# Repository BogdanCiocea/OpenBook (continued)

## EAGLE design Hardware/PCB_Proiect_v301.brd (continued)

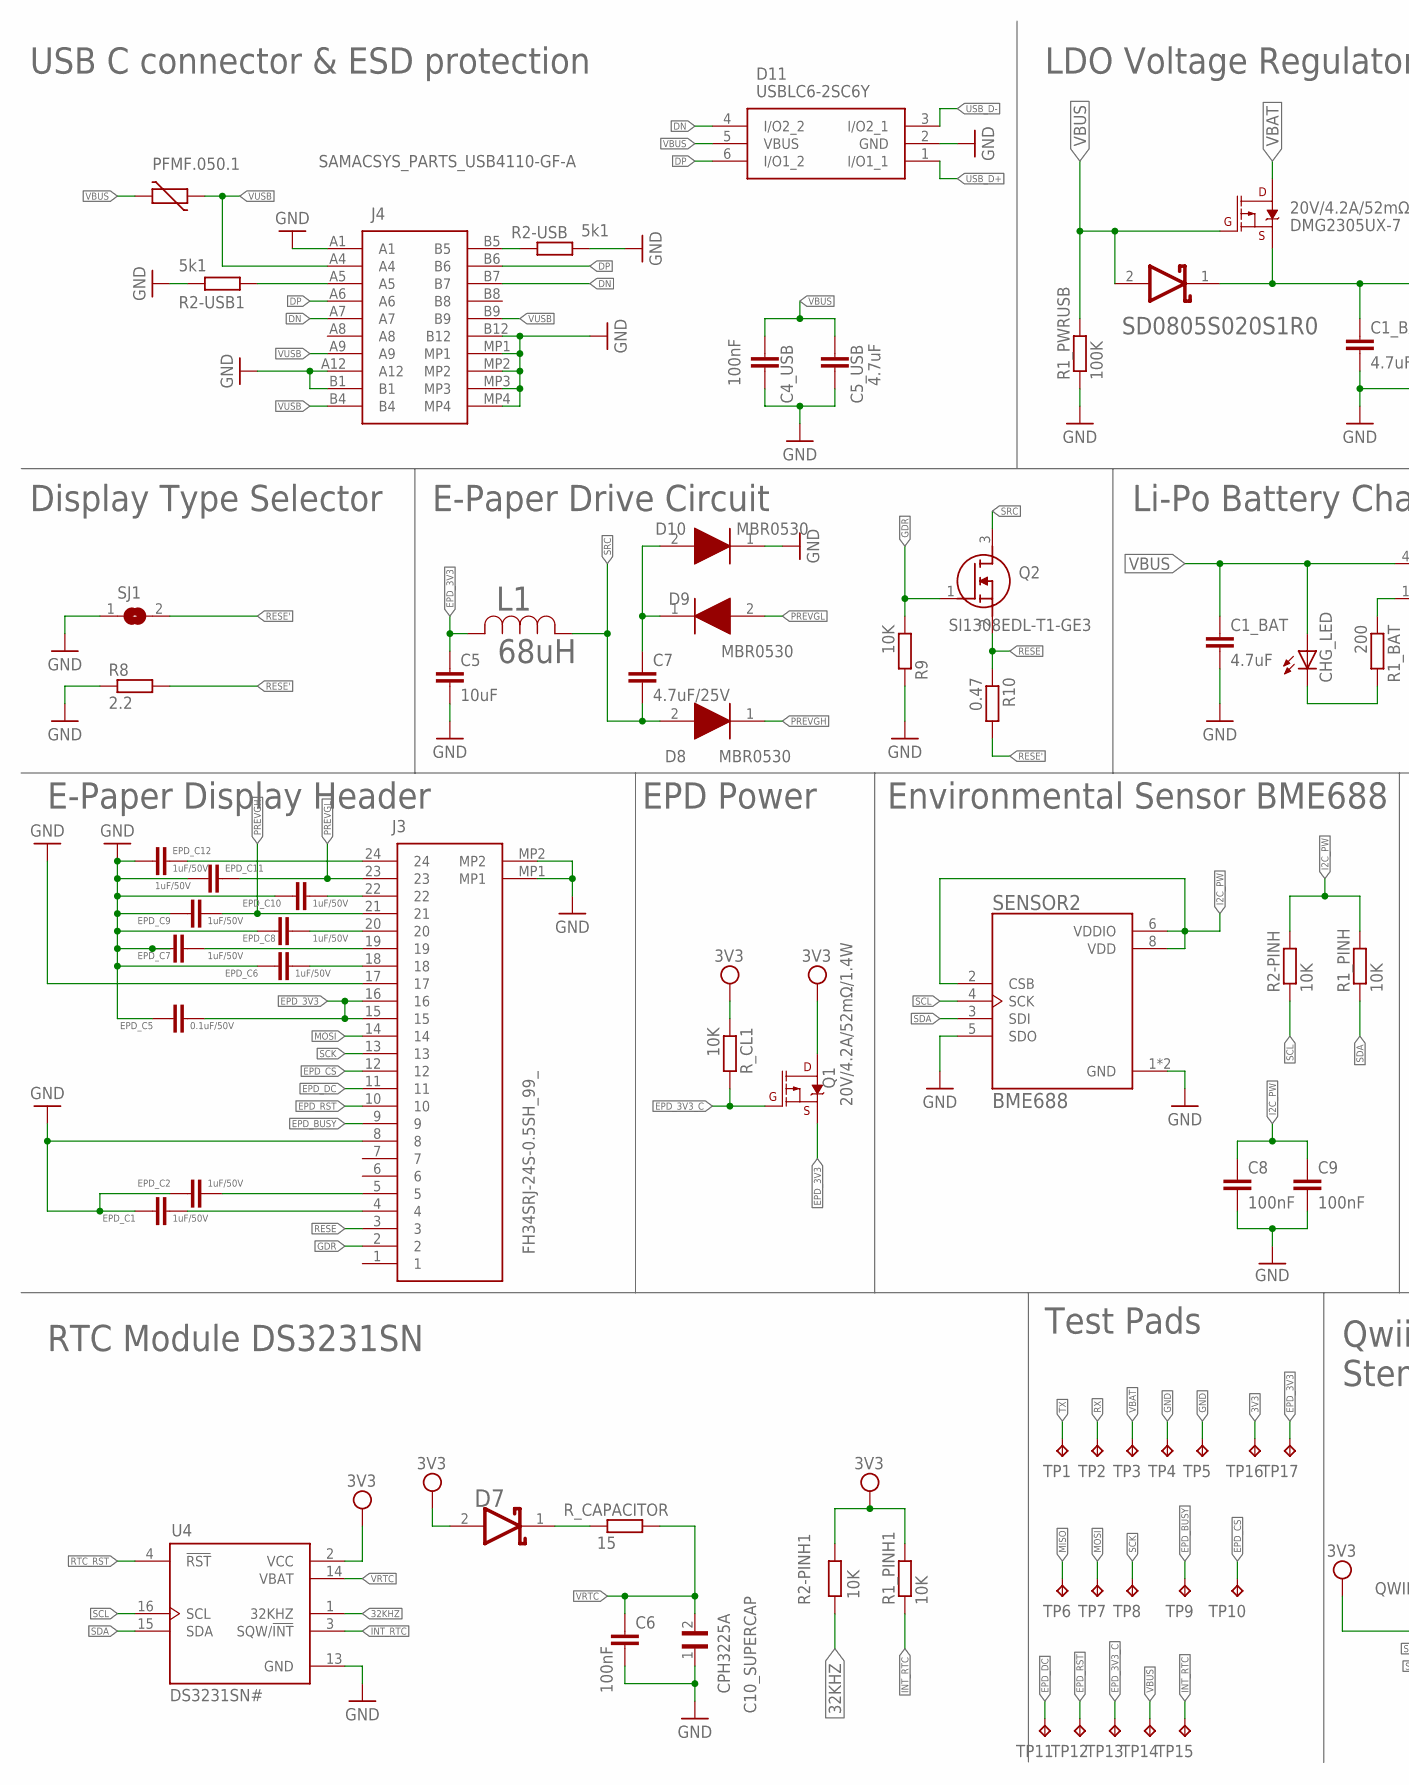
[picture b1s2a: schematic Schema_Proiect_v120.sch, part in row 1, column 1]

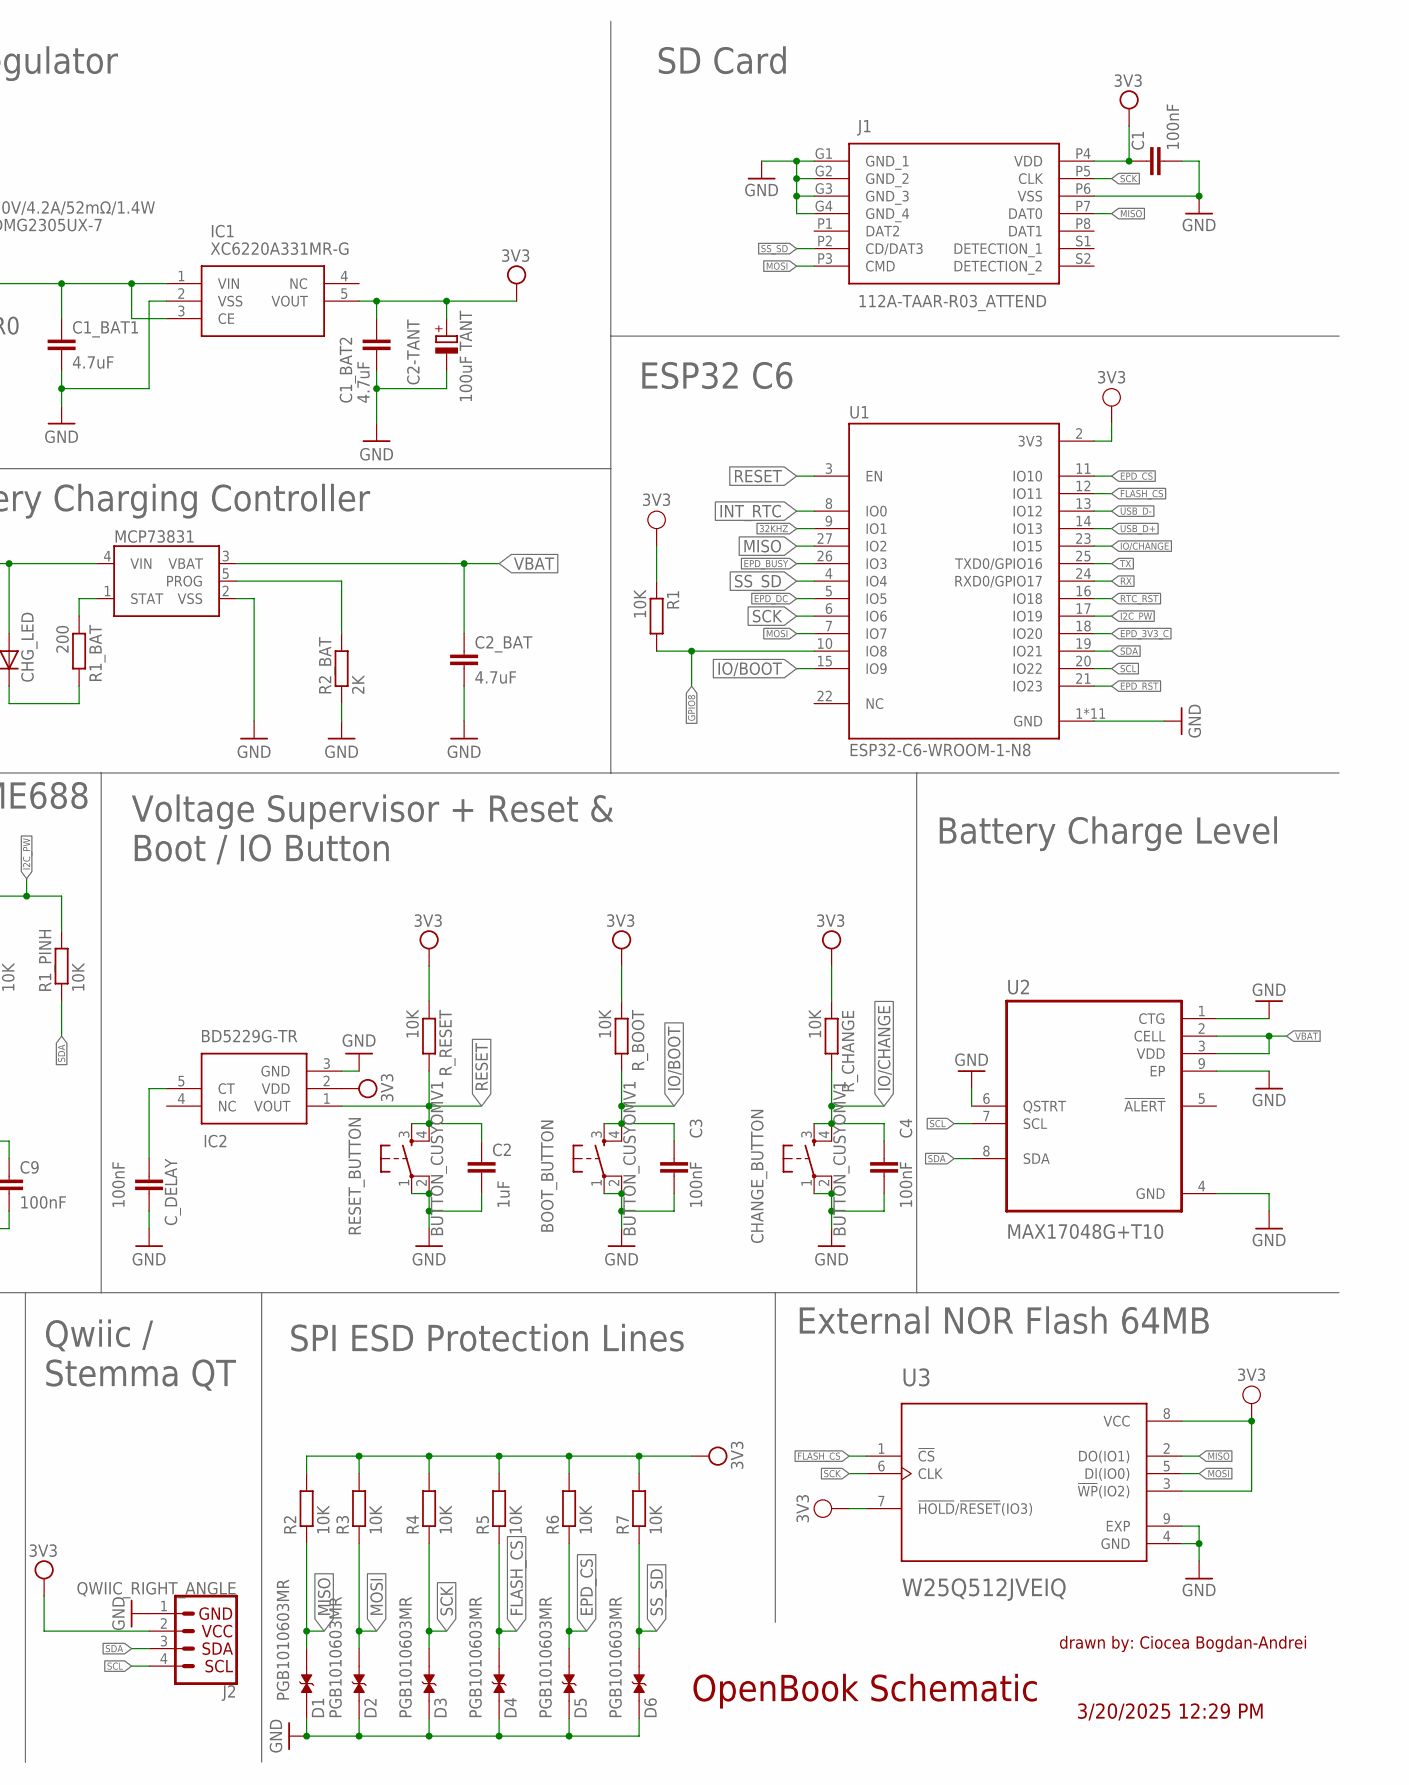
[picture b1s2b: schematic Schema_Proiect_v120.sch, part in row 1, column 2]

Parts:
BOOT_BUTTON: BUTTON_CUSYOMV1; MYBUTTON
C1, C3, C4, C4_USB, C6, C8, C9: 100nF; EAGLE-LTSPICE_C0402
C1_BAT, C1_BAT1, C1_BAT2, C2_BAT, C5_USB: 4.7uF; EAGLE-LTSPICE_C0402
C2: 1uF; EAGLE-LTSPICE_C0402
C2-TANT: 100uF TANT; RCL_CT3528
C5: 10uF; EAGLE-LTSPICE_C0402
C7: 4.7uF/25V; EAGLE-LTSPICE_C0402
C10_SUPERCAP: CPH3225A; CAPCP3225X100N
CHANGE_BUTTON: BUTTON_CUSYOMV1; MYBUTTON
CHG_LED: ADAFRUIT_LEDCHIP-LED0603; ADAFRUIT_CHIP-LED0603
C_DELAY: 100nF; EAGLE-LTSPICE_C0402
D1, D2, D3, D4, D5, D6: PGB1010603MR; DIOC1608X36N
D7: SD0805S020S1R0; ESP32_WROVER_AVX---SD0805S020S1R0_AVX_SD0805S020S1R0_0
D8, D9, D10: MBR0530; SOD3716X135N
D11: USBLC6-2SC6Y; SOT95P280X145-6N
DMG2305UX-7: 20V/4.2A/52mΩ/1.4W; ESP32_WROVER_SPARKFUN-DISCRETESEMI_SOT23-3
EPD_C1, EPD_C2, EPD_C6, EPD_C7, EPD_C8, EPD_C9, EPD_C10, EPD_C11, EPD_C12: 1uF/50V; EAGLE-LTSPICE_C0402
EPD_C5: 0.1uF/50V; EAGLE-LTSPICE_C0402
IC1: XC6220A331MR-G; SOT95P280X120-5N
IC2: BD5229G-TR; SOT95P280X125-5N
J1: 112A-TAAR-R03_ATTEND; 112ATAARR03ATTEND
J2: QWIIC_RIGHT_ANGLE; JST04_1MM_RA
J3: FH34SRJ-24S-0.5SH_99_; FH34SRJ24S05SH99
J4: SAMACSYS_PARTS_USB4110-GF-A; SAMACSYS_PARTS_USB4110GFA
L1: 68uH; IND_4828-WE-TPC_WRE
MCP73831: ESP32_WROVER_SPARKFUN-IC-POWER_MCP73831; ESP32_WROVER_SPARKFUN-IC-POWER_SOT23-5
PFMF.050.1: ESP32C6_VARISTORCN1812; ESP32C6_VARISTOR_CT/CN1812
Q1: 20V/4.2A/52mΩ/1.4W; ESP32_WROVER_SPARKFUN-DISCRETESEMI_SOT23-3
Q2: SI1308EDL-T1-GE3; SOT65P210X110-3N
R1, R1_PINH, R1_PINH1, R2, R2-PINH, R2-PINH1, R3, R4, R5, R6, R7, R9: 10K; ESP32_WROVER_EAGLE-LTSPICE_R0402
R1_BAT: 200; ESP32_WROVER_EAGLE-LTSPICE_R0402
R1_PWRUSB: 100K; ESP32_WROVER_EAGLE-LTSPICE_R0402
R2-USB, R2-USB1: 5k1; ESP32_WROVER_EAGLE-LTSPICE_R0402
R2_BAT: 2K; ESP32_WROVER_EAGLE-LTSPICE_R0402
R8: 2.2; ESP32_WROVER_EAGLE-LTSPICE_R0402
R10: 0.47; ESP32_WROVER_EAGLE-LTSPICE_R0402
RESET_BUTTON: BUTTON_CUSYOMV1; MYBUTTON
R_BOOT: 10K; ESP32_WROVER_EAGLE-LTSPICE_R0402
R_CAPACITOR: 15; ESP32_WROVER_EAGLE-LTSPICE_R0402
R_CHANGE: 10K; ESP32_WROVER_EAGLE-LTSPICE_R0402
R_CL1: 10K; ESP32_WROVER_EAGLE-LTSPICE_R0402
R_RESET: 10K; ESP32_WROVER_EAGLE-LTSPICE_R0402
SD0805S020S1R0: ESP32_WROVER_AVX---SD0805S020S1R0_AVX_SD0805S020S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; ESP32_WROVER_AVX---SD0805S020S1R0_AVX_SD0805S020S1R0_0
SENSOR2: BME688; ESP32_WROVER_BME680_PSON80P300X300X100-8N
SJ1: SJ
TP1: TX; TP20R
TP2: RX; TP20R
TP3: VBAT; TP20R
TP4, TP5: GND; TP20R
TP6: MISO; TP20R
TP7: MOSI; TP20R
TP8: SCK; TP20R
TP9: EPD_BUSY; TP20R
TP10: EPD_CS; TP20R
TP11: EPD_DC; TP20R
TP12: EPD_RST; TP20R
TP13: EPD_3V3_C; TP20R
TP14: VBUS; TP20R
TP15: INT_RTC; TP20R
TP16: 3V3; TP20R
TP17: EPD_3V3; TP20R
U1: ESP32-C6-WROOM-1-N8; XCVR_ESP32-C6-WROOM-1-N8
U2: MAX17048G+T10; SON50P200X200X80-9N
U3: W25Q512JVEIQ; SON127P600X800X80-9N
U4: DS3231SN#; SOIC127P1032X265-16N

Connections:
3V3: C1.1, C1_BAT2.1, C2-TANT.+, D7.2 (ANODE), IC1.5 (VOUT), IC2.2 (VDD), J1.P4 (VDD), J2.2, Q1.3 (D), R1.1, R1_PINH1.2, R2.2, R2-PINH1.1, R3.2, R4.2, R5.2, R6.2, R7.2, R_BOOT.1, R_CHANGE.1, R_CL1.1, R_RESET.1, TP16.TP, U1.2 (3V3), U3.3 (!WP!(IO2)), U3.7 (!HOLD!/!RESET!(IO3)), U3.8 (VCC), U4.2 (VCC)
32KHZ: R2-PINH1.2, U1.9 (IO1), U4.1 (32KHZ)
DN: D11.4 (I/O2_2), J4.A7, J4.B7
DP: D11.6 (I/O1_2), J4.A6, J4.B6
EPD_3V3: C5.1, EPD_C5.1, J3.15, J3.16, L1.2, Q1.2 (S), TP17.TP
EPD_3V3_C: Q1.1 (G), R_CL1.2, TP13.TP, U1.18 (IO20)
EPD_BUSY: J3.9, TP9.TP, U1.26 (IO3)
EPD_CS: D5.2, J3.12, R6.1, TP10.TP, U1.11 (IO10)
EPD_DC: J3.11, TP11.TP, U1.5 (IO5)
EPD_RST: J3.10, TP12.TP, U1.21 (IO23)
FLASH_CS: D4.2, R5.1, U1.12 (IO11), U3.1 (!CS)
GDR: J3.2, Q2.1 (G), R9.1
GND: BOOT_BUTTON.1, BOOT_BUTTON.2, C1.2, C1_BAT.2, C1_BAT1.2, C1_BAT2.2, C2.2, C2-TANT.-, C2_BAT.2, C3.2, C4.2, C4_USB.2, C5.2, C5_USB.2, C6.2, C8.2, C9.2, C10_SUPERCAP.1, CHANGE_BUTTON.1, CHANGE_BUTTON.2, C_DELAY.2, D1.1, D2.1, D3.1, D4.1, D5.1, D6.1, D10.1 (K), D11.2 (GND), EPD_C1.2, EPD_C2.2, EPD_C5.2, EPD_C6.2, EPD_C7.2, EPD_C8.2, EPD_C9.2, EPD_C10.2, EPD_C11.2, EPD_C12.2, IC1.2 (VSS), IC2.3 (GND), J1.G1 (GND_1), J1.G2 (GND_2), J1.G3 (GND_3), J1.G4 (GND_4), J1.P6 (VSS), J2.1, J3.8, J3.17, J3.MP1, J3.MP2, J4.A1, J4.A12, J4.B1, J4.B12, J4.MP1, J4.MP2, J4.MP3, J4.MP4, MCP73831.2 (VSS), R1_PWRUSB.1, R2-USB.2, R2-USB1.1, R2_BAT.1, R8.1, R9.2, RESET_BUTTON.1, RESET_BUTTON.2, SENSOR2.1 (GND), SENSOR2.5 (SDO), SENSOR2.7 (GND), SJ1.1, TP4.TP, TP5.TP, U1.1 (GND), U1.28 (GND), U1.29_1 (GND), U1.29_2 (GND), U1.29_3 (GND), U1.29_4 (GND), U1.29_5 (GND), U1.29_6 (GND), U1.29_7 (GND), U1.29_8 (GND), U1.29_9 (GND), U2.1 (CTG), U2.4 (GND), U2.6 (QSTRT), U2.9 (EP), U3.4 (GND), U3.9 (EXP), U4.13 (GND)
GPIO8: R1.2, U1.10 (IO8)
I2C_PW: C8.1, C9.1, R1_PINH.2, R2-PINH.2, SENSOR2.2 (CSB), SENSOR2.6 (VDDIO), SENSOR2.8 (VDD), U1.17 (IO19)
INT_RTC: R1_PINH1.1, TP15.TP, U1.8 (IO0), U4.3 (SQW/!INT)
IO/BOOT: BOOT_BUTTON.3, BOOT_BUTTON.4, C3.1, R_BOOT.2, U1.15 (IO9)
IO/CHANGE: C4.1, CHANGE_BUTTON.3, CHANGE_BUTTON.4, R_CHANGE.2, U1.23 (IO15)
MISO: D1.2, J1.P7 (DAT0), R2.1, TP6.TP, U1.27 (IO2), U3.2 (DO(IO1))
MOSI: D2.2, J1.P3 (CMD), J3.14, R3.1, TP7.TP, U1.7 (IO7), U3.5 (DI(IO0))
unnamed: CHG_LED.C, R1_BAT.2
unnamed: D7.1 (CATHODE), R_CAPACITOR.2
unnamed: C_DELAY.1, IC2.5 (CT)
unnamed: C1_BAT1.1, DMG2305UX-7.2 (S), IC1.1 (VIN), IC1.3 (CE), SD0805S020S1R0.1 (CATHODE)
unnamed: MCP73831.5 (PROG), R2_BAT.2
unnamed: MCP73831.1 (STAT), R1_BAT.1
unnamed: EPD_C12.1, J3.24
unnamed: EPD_C7.1, J3.19
unnamed: EPD_C1.1, J3.4
unnamed: EPD_C2.1, J3.5
unnamed: EPD_C10.1, J3.22
unnamed: EPD_C8.1, J3.20
unnamed: C7.1, D9.1 (K), D10.2 (A)
unnamed: J4.B5, R2-USB.1
unnamed: J4.A5, R2-USB1.2
unnamed: EPD_C6.1, J3.18
PREVGH: D8.1 (K), EPD_C9.1, J3.21
PREVGL: D9.2 (A), EPD_C11.1, J3.23
RESE: J3.3, Q2.2 (S), R10.1
RESE': R8.2, R10.2, SJ1.2
RESET: C2.1, IC2.1 (VOUT), RESET_BUTTON.3, RESET_BUTTON.4, R_RESET.2, U1.3 (EN)
RTC_RST: U1.16 (IO18), U4.4 (!RST)
RX: TP2.TP, U1.24 (RXD0/GPIO17)
SCK: D3.2, J1.P5 (CLK), J3.13, R4.1, TP8.TP, U1.6 (IO6), U3.6 (CLK)
SCL: J2.4, R2-PINH.1, SENSOR2.4 (SCK), U1.20 (IO22), U2.7 (SCL), U4.16 (SCL)
SDA: J2.3, R1_PINH.1, SENSOR2.3 (SDI), U1.19 (IO21), U2.8 (SDA), U4.15 (SDA)
SRC: C7.2, D8.2 (A), L1.1, Q2.3 (D)
SS_SD: D6.2, J1.P2 (CD/DAT3), R7.1, U1.4 (IO4)
TX: TP1.TP, U1.25 (TXD0/GPIO16)
USB_D+: D11.1 (I/O1_1), U1.14 (IO13)
USB_D-: D11.3 (I/O2_1), U1.13 (IO12)
VBAT: C2_BAT.1, DMG2305UX-7.3 (D), MCP73831.3 (VBAT), TP3.TP, U2.2 (CELL), U2.3 (VDD)
VBUS: C1_BAT.1, C4_USB.1, C5_USB.1, CHG_LED.A, D11.5 (VBUS), DMG2305UX-7.1 (G), MCP73831.4 (VIN), PFMF.050.1.2, R1_PWRUSB.2, SD0805S020S1R0.2 (ANODE), TP14.TP
VRTC: C6.1, C10_SUPERCAP.2, R_CAPACITOR.1, U4.14 (VBAT)
VUSB: J4.A4, J4.A9, J4.B4, J4.B9, PFMF.050.1.1

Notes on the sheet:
drawn by: Ciocea Bogdan-Andrei
OpenBook Schematic
External NOR Flash 64MB
Battery Charge Level
SD Card
SPI ESD Protection Lines
Qwiic / Stemma QT
Test Pads
Voltage Supervisor + Reset & Boot / IO Button
ESP32 C6
RTC Module DS3231SN
USB C connector & ESD protection
LDO Voltage Regulator
Li-Po Battery Charging Controller
E-Paper Drive Circuit
Display Type Selector
Environmental Sensor BME688
EPD Power
E-Paper Display Header
3/20/2025 12:29 PM

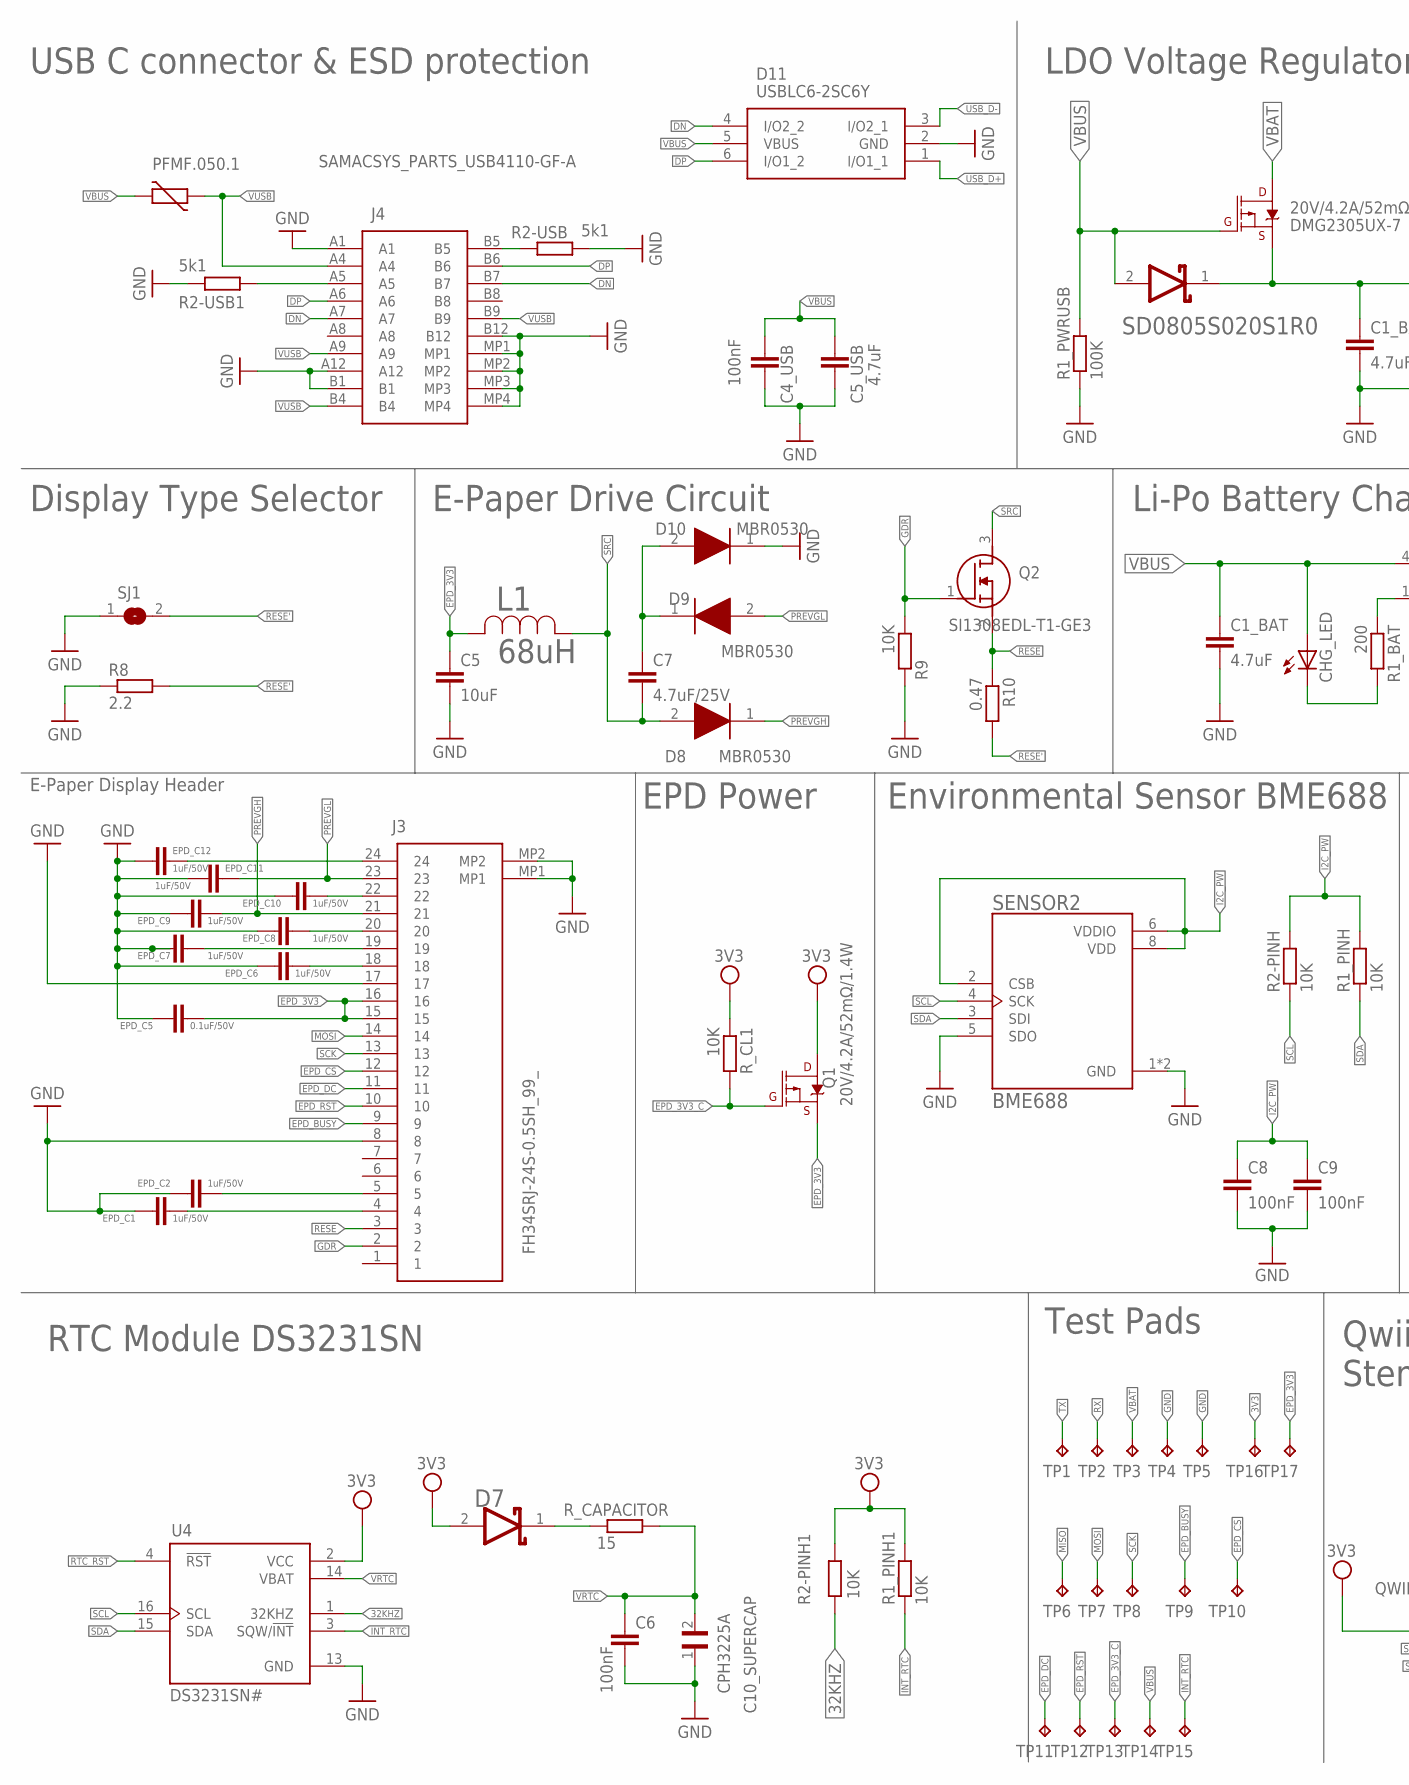
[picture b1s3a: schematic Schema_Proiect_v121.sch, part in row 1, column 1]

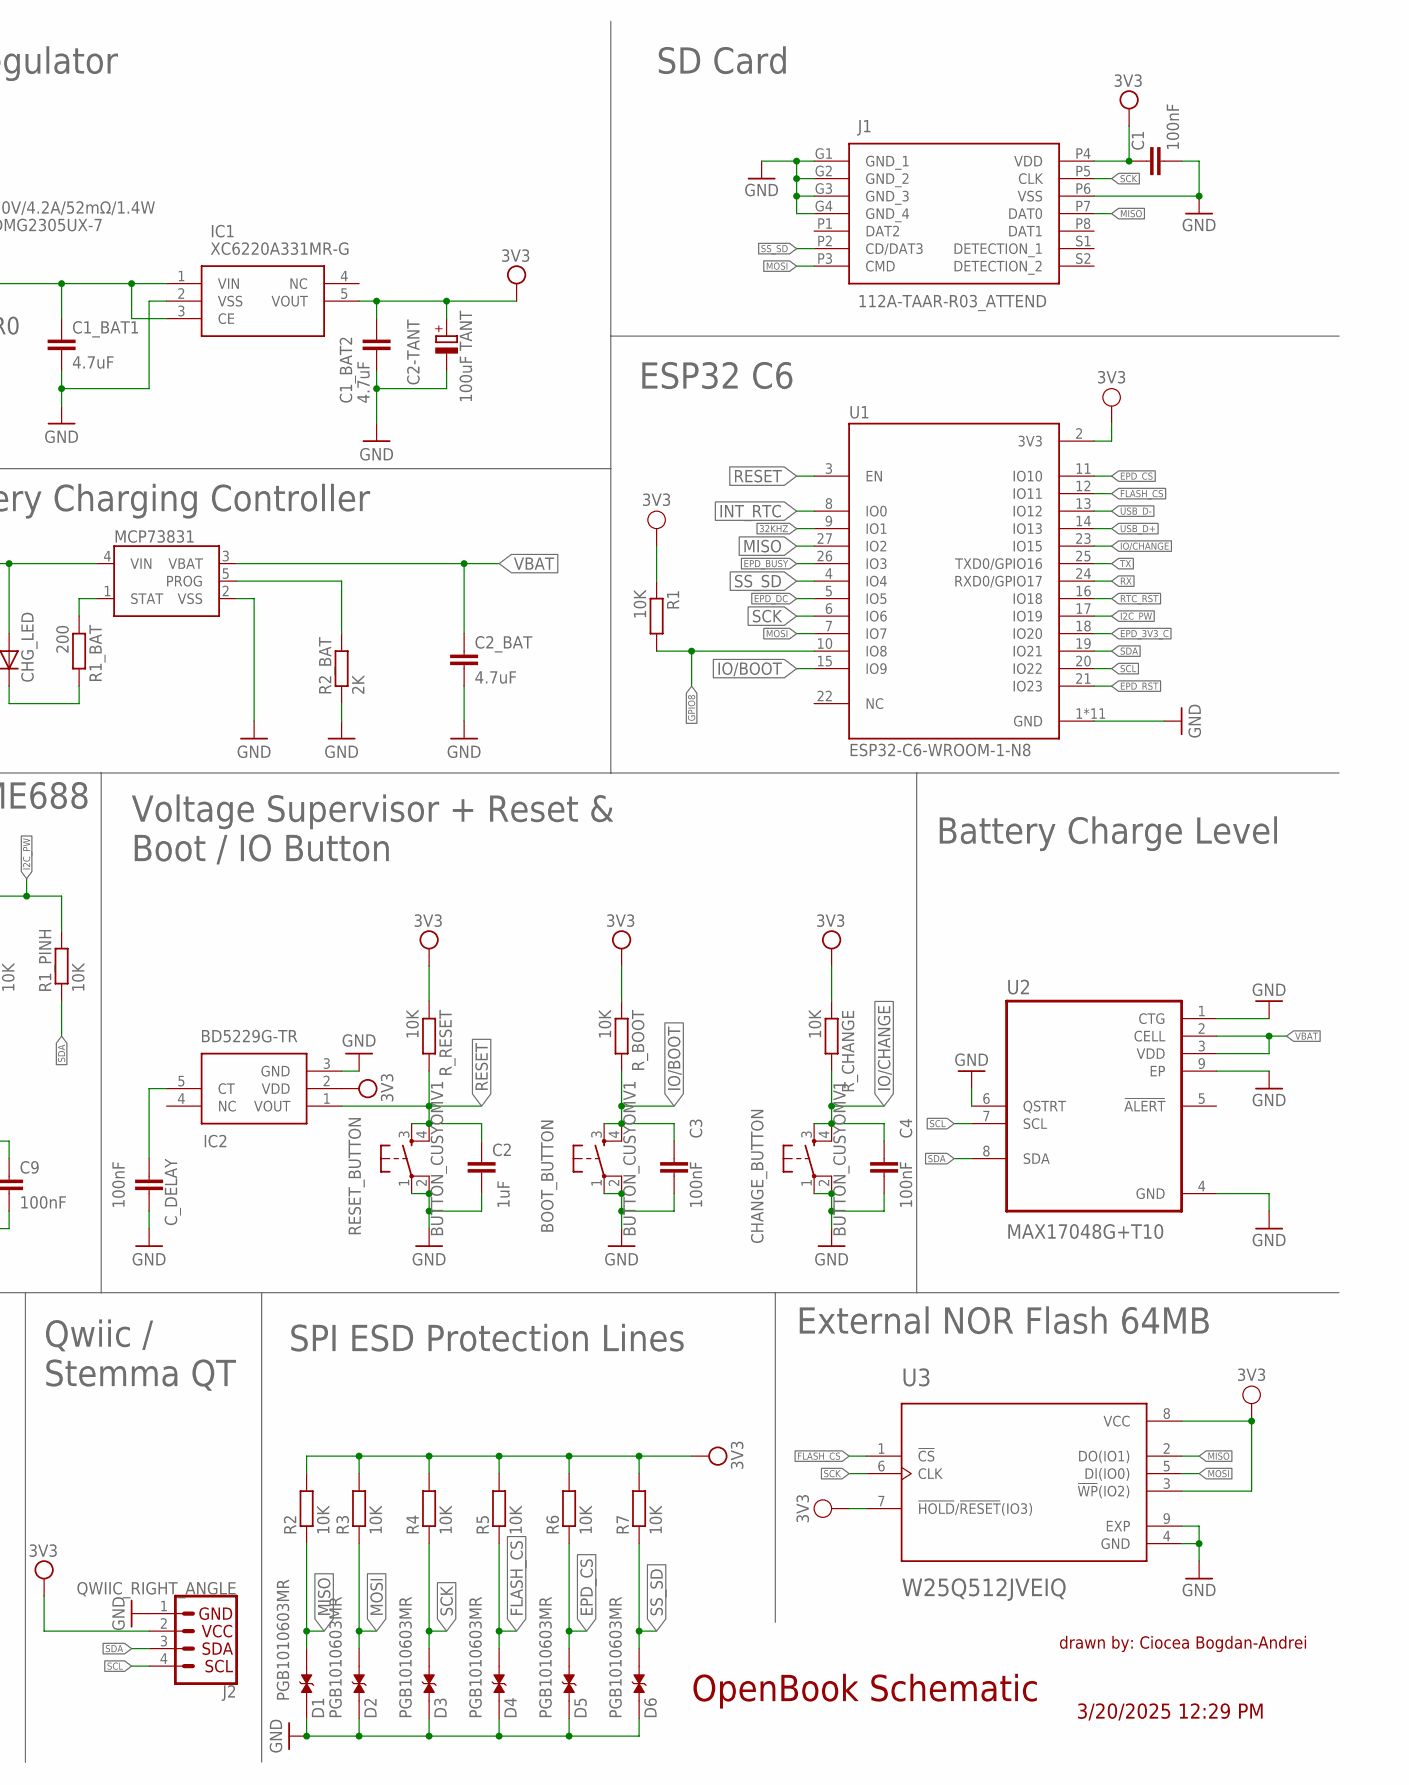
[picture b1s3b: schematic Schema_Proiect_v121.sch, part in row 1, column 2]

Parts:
BOOT_BUTTON: BUTTON_CUSYOMV1; MYBUTTON
C1, C3, C4, C4_USB, C6, C8, C9: 100nF; EAGLE-LTSPICE_C0402
C1_BAT, C1_BAT1, C1_BAT2, C2_BAT, C5_USB: 4.7uF; EAGLE-LTSPICE_C0402
C2: 1uF; EAGLE-LTSPICE_C0402
C2-TANT: 100uF TANT; RCL_CT3528
C5: 10uF; EAGLE-LTSPICE_C0402
C7: 4.7uF/25V; EAGLE-LTSPICE_C0402
C10_SUPERCAP: CPH3225A; CAPCP3225X100N
CHANGE_BUTTON: BUTTON_CUSYOMV1; MYBUTTON
CHG_LED: ADAFRUIT_LEDCHIP-LED0603; ADAFRUIT_CHIP-LED0603
C_DELAY: 100nF; EAGLE-LTSPICE_C0402
D1, D2, D3, D4, D5, D6: PGB1010603MR; DIOC1608X36N
D7: SD0805S020S1R0; ESP32_WROVER_AVX---SD0805S020S1R0_AVX_SD0805S020S1R0_0
D8, D9, D10: MBR0530; SOD3716X135N
D11: USBLC6-2SC6Y; SOT95P280X145-6N
DMG2305UX-7: 20V/4.2A/52mΩ/1.4W; ESP32_WROVER_SPARKFUN-DISCRETESEMI_SOT23-3
EPD_C1, EPD_C2, EPD_C6, EPD_C7, EPD_C8, EPD_C9, EPD_C10, EPD_C11, EPD_C12: 1uF/50V; EAGLE-LTSPICE_C0402
EPD_C5: 0.1uF/50V; EAGLE-LTSPICE_C0402
IC1: XC6220A331MR-G; SOT95P280X120-5N
IC2: BD5229G-TR; SOT95P280X125-5N
J1: 112A-TAAR-R03_ATTEND; 112ATAARR03ATTEND
J2: QWIIC_RIGHT_ANGLE; JST04_1MM_RA
J3: FH34SRJ-24S-0.5SH_99_; FH34SRJ24S05SH99
J4: SAMACSYS_PARTS_USB4110-GF-A; SAMACSYS_PARTS_USB4110GFA
L1: 68uH; IND_4828-WE-TPC_WRE
MCP73831: ESP32_WROVER_SPARKFUN-IC-POWER_MCP73831; ESP32_WROVER_SPARKFUN-IC-POWER_SOT23-5
PFMF.050.1: ESP32C6_VARISTORCN1812; ESP32C6_VARISTOR_CT/CN1812
Q1: 20V/4.2A/52mΩ/1.4W; ESP32_WROVER_SPARKFUN-DISCRETESEMI_SOT23-3
Q2: SI1308EDL-T1-GE3; SOT65P210X110-3N
R1, R1_PINH, R1_PINH1, R2, R2-PINH, R2-PINH1, R3, R4, R5, R6, R7, R9: 10K; ESP32_WROVER_EAGLE-LTSPICE_R0402
R1_BAT: 200; ESP32_WROVER_EAGLE-LTSPICE_R0402
R1_PWRUSB: 100K; ESP32_WROVER_EAGLE-LTSPICE_R0402
R2-USB, R2-USB1: 5k1; ESP32_WROVER_EAGLE-LTSPICE_R0402
R2_BAT: 2K; ESP32_WROVER_EAGLE-LTSPICE_R0402
R8: 2.2; ESP32_WROVER_EAGLE-LTSPICE_R0402
R10: 0.47; ESP32_WROVER_EAGLE-LTSPICE_R0402
RESET_BUTTON: BUTTON_CUSYOMV1; MYBUTTON
R_BOOT: 10K; ESP32_WROVER_EAGLE-LTSPICE_R0402
R_CAPACITOR: 15; ESP32_WROVER_EAGLE-LTSPICE_R0402
R_CHANGE: 10K; ESP32_WROVER_EAGLE-LTSPICE_R0402
R_CL1: 10K; ESP32_WROVER_EAGLE-LTSPICE_R0402
R_RESET: 10K; ESP32_WROVER_EAGLE-LTSPICE_R0402
SD0805S020S1R0: ESP32_WROVER_AVX---SD0805S020S1R0_AVX_SD0805S020S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; ESP32_WROVER_AVX---SD0805S020S1R0_AVX_SD0805S020S1R0_0
SENSOR2: BME688; ESP32_WROVER_BME680_PSON80P300X300X100-8N
SJ1: SJ
TP1: TX; TP20R
TP2: RX; TP20R
TP3: VBAT; TP20R
TP4, TP5: GND; TP20R
TP6: MISO; TP20R
TP7: MOSI; TP20R
TP8: SCK; TP20R
TP9: EPD_BUSY; TP20R
TP10: EPD_CS; TP20R
TP11: EPD_DC; TP20R
TP12: EPD_RST; TP20R
TP13: EPD_3V3_C; TP20R
TP14: VBUS; TP20R
TP15: INT_RTC; TP20R
TP16: 3V3; TP20R
TP17: EPD_3V3; TP20R
U1: ESP32-C6-WROOM-1-N8; XCVR_ESP32-C6-WROOM-1-N8
U2: MAX17048G+T10; SON50P200X200X80-9N
U3: W25Q512JVEIQ; SON127P600X800X80-9N
U4: DS3231SN#; SOIC127P1032X265-16N

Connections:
3V3: C1.1, C1_BAT2.1, C2-TANT.+, D7.2 (ANODE), IC1.5 (VOUT), IC2.2 (VDD), J1.P4 (VDD), J2.2, Q1.3 (D), R1.1, R1_PINH1.2, R2.2, R2-PINH1.1, R3.2, R4.2, R5.2, R6.2, R7.2, R_BOOT.1, R_CHANGE.1, R_CL1.1, R_RESET.1, TP16.TP, U1.2 (3V3), U3.3 (!WP!(IO2)), U3.7 (!HOLD!/!RESET!(IO3)), U3.8 (VCC), U4.2 (VCC)
32KHZ: R2-PINH1.2, U1.9 (IO1), U4.1 (32KHZ)
DN: D11.4 (I/O2_2), J4.A7, J4.B7
DP: D11.6 (I/O1_2), J4.A6, J4.B6
EPD_3V3: C5.1, EPD_C5.1, J3.15, J3.16, L1.2, Q1.2 (S), TP17.TP
EPD_3V3_C: Q1.1 (G), R_CL1.2, TP13.TP, U1.18 (IO20)
EPD_BUSY: J3.9, TP9.TP, U1.26 (IO3)
EPD_CS: D5.2, J3.12, R6.1, TP10.TP, U1.11 (IO10)
EPD_DC: J3.11, TP11.TP, U1.5 (IO5)
EPD_RST: J3.10, TP12.TP, U1.21 (IO23)
FLASH_CS: D4.2, R5.1, U1.12 (IO11), U3.1 (!CS)
GDR: J3.2, Q2.1 (G), R9.1
GND: BOOT_BUTTON.1, BOOT_BUTTON.2, C1.2, C1_BAT.2, C1_BAT1.2, C1_BAT2.2, C2.2, C2-TANT.-, C2_BAT.2, C3.2, C4.2, C4_USB.2, C5.2, C5_USB.2, C6.2, C8.2, C9.2, C10_SUPERCAP.1, CHANGE_BUTTON.1, CHANGE_BUTTON.2, C_DELAY.2, D1.1, D2.1, D3.1, D4.1, D5.1, D6.1, D10.1 (K), D11.2 (GND), EPD_C1.2, EPD_C2.2, EPD_C5.2, EPD_C6.2, EPD_C7.2, EPD_C8.2, EPD_C9.2, EPD_C10.2, EPD_C11.2, EPD_C12.2, IC1.2 (VSS), IC2.3 (GND), J1.G1 (GND_1), J1.G2 (GND_2), J1.G3 (GND_3), J1.G4 (GND_4), J1.P6 (VSS), J2.1, J3.8, J3.17, J3.MP1, J3.MP2, J4.A1, J4.A12, J4.B1, J4.B12, J4.MP1, J4.MP2, J4.MP3, J4.MP4, MCP73831.2 (VSS), R1_PWRUSB.1, R2-USB.2, R2-USB1.1, R2_BAT.1, R8.1, R9.2, RESET_BUTTON.1, RESET_BUTTON.2, SENSOR2.1 (GND), SENSOR2.5 (SDO), SENSOR2.7 (GND), SJ1.1, TP4.TP, TP5.TP, U1.1 (GND), U1.28 (GND), U1.29_1 (GND), U1.29_2 (GND), U1.29_3 (GND), U1.29_4 (GND), U1.29_5 (GND), U1.29_6 (GND), U1.29_7 (GND), U1.29_8 (GND), U1.29_9 (GND), U2.1 (CTG), U2.4 (GND), U2.6 (QSTRT), U2.9 (EP), U3.4 (GND), U3.9 (EXP), U4.13 (GND)
GPIO8: R1.2, U1.10 (IO8)
I2C_PW: C8.1, C9.1, R1_PINH.2, R2-PINH.2, SENSOR2.2 (CSB), SENSOR2.6 (VDDIO), SENSOR2.8 (VDD), U1.17 (IO19)
INT_RTC: R1_PINH1.1, TP15.TP, U1.8 (IO0), U4.3 (SQW/!INT)
IO/BOOT: BOOT_BUTTON.3, BOOT_BUTTON.4, C3.1, R_BOOT.2, U1.15 (IO9)
IO/CHANGE: C4.1, CHANGE_BUTTON.3, CHANGE_BUTTON.4, R_CHANGE.2, U1.23 (IO15)
MISO: D1.2, J1.P7 (DAT0), R2.1, TP6.TP, U1.27 (IO2), U3.2 (DO(IO1))
MOSI: D2.2, J1.P3 (CMD), J3.14, R3.1, TP7.TP, U1.7 (IO7), U3.5 (DI(IO0))
unnamed: CHG_LED.C, R1_BAT.2
unnamed: D7.1 (CATHODE), R_CAPACITOR.2
unnamed: C_DELAY.1, IC2.5 (CT)
unnamed: C1_BAT1.1, DMG2305UX-7.2 (S), IC1.1 (VIN), IC1.3 (CE), SD0805S020S1R0.1 (CATHODE)
unnamed: MCP73831.5 (PROG), R2_BAT.2
unnamed: MCP73831.1 (STAT), R1_BAT.1
unnamed: EPD_C12.1, J3.24
unnamed: EPD_C7.1, J3.19
unnamed: EPD_C1.1, J3.4
unnamed: EPD_C2.1, J3.5
unnamed: EPD_C10.1, J3.22
unnamed: EPD_C8.1, J3.20
unnamed: C7.1, D9.1 (K), D10.2 (A)
unnamed: J4.B5, R2-USB.1
unnamed: J4.A5, R2-USB1.2
unnamed: EPD_C6.1, J3.18
PREVGH: D8.1 (K), EPD_C9.1, J3.21
PREVGL: D9.2 (A), EPD_C11.1, J3.23
RESE: J3.3, Q2.2 (S), R10.1
RESE': R8.2, R10.2, SJ1.2
RESET: C2.1, IC2.1 (VOUT), RESET_BUTTON.3, RESET_BUTTON.4, R_RESET.2, U1.3 (EN)
RTC_RST: U1.16 (IO18), U4.4 (!RST)
RX: TP2.TP, U1.24 (RXD0/GPIO17)
SCK: D3.2, J1.P5 (CLK), J3.13, R4.1, TP8.TP, U1.6 (IO6), U3.6 (CLK)
SCL: J2.4, R2-PINH.1, SENSOR2.4 (SCK), U1.20 (IO22), U2.7 (SCL), U4.16 (SCL)
SDA: J2.3, R1_PINH.1, SENSOR2.3 (SDI), U1.19 (IO21), U2.8 (SDA), U4.15 (SDA)
SRC: C7.2, D8.2 (A), L1.1, Q2.3 (D)
SS_SD: D6.2, J1.P2 (CD/DAT3), R7.1, U1.4 (IO4)
TX: TP1.TP, U1.25 (TXD0/GPIO16)
USB_D+: D11.1 (I/O1_1), U1.14 (IO13)
USB_D-: D11.3 (I/O2_1), U1.13 (IO12)
VBAT: C2_BAT.1, DMG2305UX-7.3 (D), MCP73831.3 (VBAT), TP3.TP, U2.2 (CELL), U2.3 (VDD)
VBUS: C1_BAT.1, C4_USB.1, C5_USB.1, CHG_LED.A, D11.5 (VBUS), DMG2305UX-7.1 (G), MCP73831.4 (VIN), PFMF.050.1.2, R1_PWRUSB.2, SD0805S020S1R0.2 (ANODE), TP14.TP
VRTC: C6.1, C10_SUPERCAP.2, R_CAPACITOR.1, U4.14 (VBAT)
VUSB: J4.A4, J4.A9, J4.B4, J4.B9, PFMF.050.1.1

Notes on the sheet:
drawn by: Ciocea Bogdan-Andrei
OpenBook Schematic
External NOR Flash 64MB
Battery Charge Level
SD Card
SPI ESD Protection Lines
Qwiic / Stemma QT
Test Pads
Voltage Supervisor + Reset & Boot / IO Button
ESP32 C6
RTC Module DS3231SN
USB C connector & ESD protection
LDO Voltage Regulator
Li-Po Battery Charging Controller
E-Paper Drive Circuit
Display Type Selector
Environmental Sensor BME688
EPD Power
E-Paper Display Header
3/20/2025 12:29 PM
